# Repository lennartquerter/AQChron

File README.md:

## AQChron

Split Staggered Ortholineair keyboard.

## LICENSE

[CC BY-NC-SA 4.0](./license.md)

## Hardware

Kicad project is in the `hardware` directory.

## Software

TODO

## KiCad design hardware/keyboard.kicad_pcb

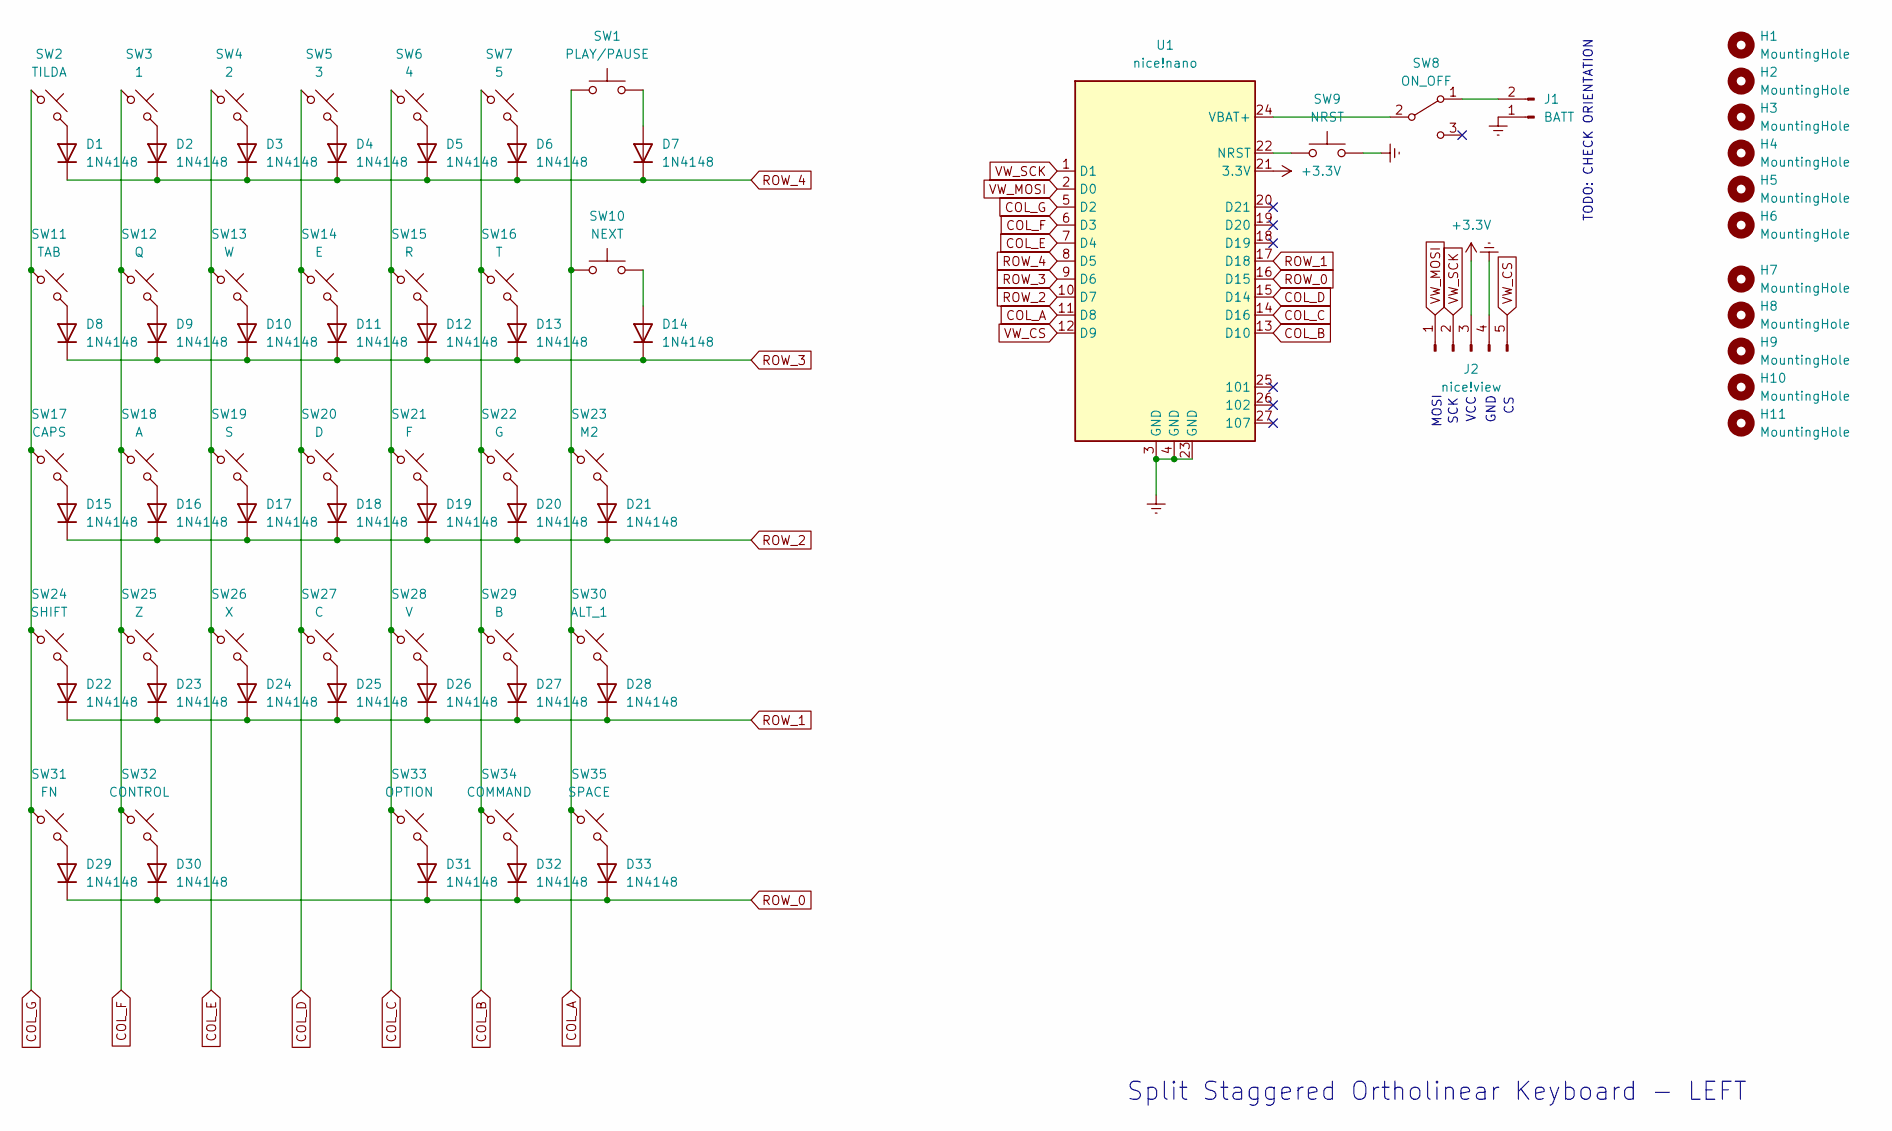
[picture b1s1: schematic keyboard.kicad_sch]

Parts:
D1, D2, D3, D4, D5, D6, D7, D8, D9, D10, D11, D12, D13, D14, D15, D16, D17, D18, D19, D20, D21, D22, D23, D24, D25, D26, D27, D28, D29, D30, D31, D32, D33: 1N4148; D_SMD-THT
H1, H2, H3, H4, H5, H6: MountingHole; MountingPin_M2
H7, H8, H9, H10, H11: MountingHole; MountingPin_M3
J1: BATT; JST_PH_S2B-PH-K_1x02_P2.00mm_Horizontal
J2: nice!view; PinHeader_1x05_P2.54mm_Vertical
SW1: PLAY/PAUSE; SW_PUSH_6mm
SW2: TILDA; Hotswap_Choc_V1V2
SW3: 1; Hotswap_Choc_V1V2
SW4: 2; Hotswap_Choc_V1V2
SW5: 3; Hotswap_Choc_V1V2
SW6: 4; Hotswap_Choc_V1V2
SW7: 5; Hotswap_Choc_V1V2
SW8: ON_OFF; Switch_MSK12C02
SW9: NRST; SW_PUSH_6mm
SW10: NEXT; SW_PUSH_6mm
SW11: TAB; Hotswap_Choc_V1V2
SW12: Q; Hotswap_Choc_V1V2
SW13: W; Hotswap_Choc_V1V2
SW14: E; Hotswap_Choc_V1V2
SW15: R; Hotswap_Choc_V1V2
SW16: T; Hotswap_Choc_V1V2
SW17: CAPS; Hotswap_Choc_V1V2
SW18: A; Hotswap_Choc_V1V2
SW19: S; Hotswap_Choc_V1V2
SW20: D; Hotswap_Choc_V1V2
SW21: F; Hotswap_Choc_V1V2
SW22: G; Hotswap_Choc_V1V2
SW23: M2; Hotswap_Choc_V1V2
SW24: SHIFT; Hotswap_Choc_V1V2
SW25: Z; Hotswap_Choc_V1V2
SW26: X; Hotswap_Choc_V1V2
SW27: C; Hotswap_Choc_V1V2
SW28: V; Hotswap_Choc_V1V2
SW29: B; Hotswap_Choc_V1V2
SW30: ALT_1; Hotswap_Choc_V1V2
SW31: FN; Hotswap_Choc_V1V2
SW32: CONTROL; Hotswap_Choc_V1V2
SW33: OPTION; Hotswap_Choc_V1V2
SW34: COMMAND; Hotswap_Choc_V1V2
SW35: SPACE; Hotswap_Choc_V1V2
U1: nice!nano

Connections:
+3.3V: J2.3, U1.21 (3.3V)
COL_A: SW1.1, SW10.1, SW23.1, SW30.1, SW35.1, U1.11 (D8)
COL_B: SW7.1, SW16.1, SW22.1, SW29.1, SW34.1, U1.13 (D10)
COL_C: SW6.1, SW15.1, SW21.1, SW28.1, SW33.1, U1.14 (D16)
COL_D: SW5.1, SW14.1, SW20.1, SW27.1, U1.15 (D14)
COL_E: SW4.1, SW13.1, SW19.1, SW26.1, U1.7 (D4)
COL_F: SW3.1, SW12.1, SW18.1, SW25.1, SW32.1, U1.6 (D3)
COL_G: SW2.1, SW11.1, SW17.1, SW24.1, SW31.1, U1.5 (D2)
GNDREF: J1.1, J2.4, SW9.2, U1.3 (GND), U1.4 (GND), U1.23 (GND)
unnamed: D1.2 (A), SW2.2
unnamed: D2.2 (A), SW3.2
unnamed: D3.2 (A), SW4.2
unnamed: D4.2 (A), SW5.2
unnamed: D5.2 (A), SW6.2
unnamed: D6.2 (A), SW7.2
unnamed: D7.2 (A), SW1.2
unnamed: D8.2 (A), SW11.2
unnamed: D9.2 (A), SW12.2
unnamed: D10.2 (A), SW13.2
unnamed: D11.2 (A), SW14.2
unnamed: D12.2 (A), SW15.2
unnamed: D13.2 (A), SW16.2
unnamed: D14.2 (A), SW10.2
unnamed: D15.2 (A), SW17.2
unnamed: D16.2 (A), SW18.2
unnamed: D17.2 (A), SW19.2
unnamed: D18.2 (A), SW20.2
unnamed: D19.2 (A), SW21.2
unnamed: D20.2 (A), SW22.2
unnamed: D21.2 (A), SW23.2
unnamed: D22.2 (A), SW24.2
unnamed: D23.2 (A), SW25.2
unnamed: D24.2 (A), SW26.2
unnamed: D25.2 (A), SW27.2
unnamed: D26.2 (A), SW28.2
unnamed: D27.2 (A), SW29.2
unnamed: D28.2 (A), SW30.2
unnamed: D29.2 (A), SW31.2
unnamed: D30.2 (A), SW32.2
unnamed: D31.2 (A), SW33.2
unnamed: D32.2 (A), SW34.2
unnamed: D33.2 (A), SW35.2
unnamed: J1.2, SW8.1 (A)
unnamed: SW8.2 (B), U1.24 (VBAT+)
unnamed: SW9.1, U1.22 (NRST)
ROW_0: D29.1 (K), D30.1 (K), D31.1 (K), D32.1 (K), D33.1 (K), U1.16 (D15)
ROW_1: D22.1 (K), D23.1 (K), D24.1 (K), D25.1 (K), D26.1 (K), D27.1 (K), D28.1 (K), U1.17 (D18)
ROW_2: D15.1 (K), D16.1 (K), D17.1 (K), D18.1 (K), D19.1 (K), D20.1 (K), D21.1 (K), U1.10 (D7)
ROW_3: D8.1 (K), D9.1 (K), D10.1 (K), D11.1 (K), D12.1 (K), D13.1 (K), D14.1 (K), U1.9 (D6)
ROW_4: D1.1 (K), D2.1 (K), D3.1 (K), D4.1 (K), D5.1 (K), D6.1 (K), D7.1 (K), U1.8 (D5)
VW_CS: J2.5, U1.12 (D9)
VW_MOSI: J2.1, U1.2 (D0)
VW_SCK: J2.2, U1.1 (D1)

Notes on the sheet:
GND
VCC
MOSI
Split Staggered Ortholinear Keyboard - LEFT
TODO: CHECK ORIENTATION
SCK

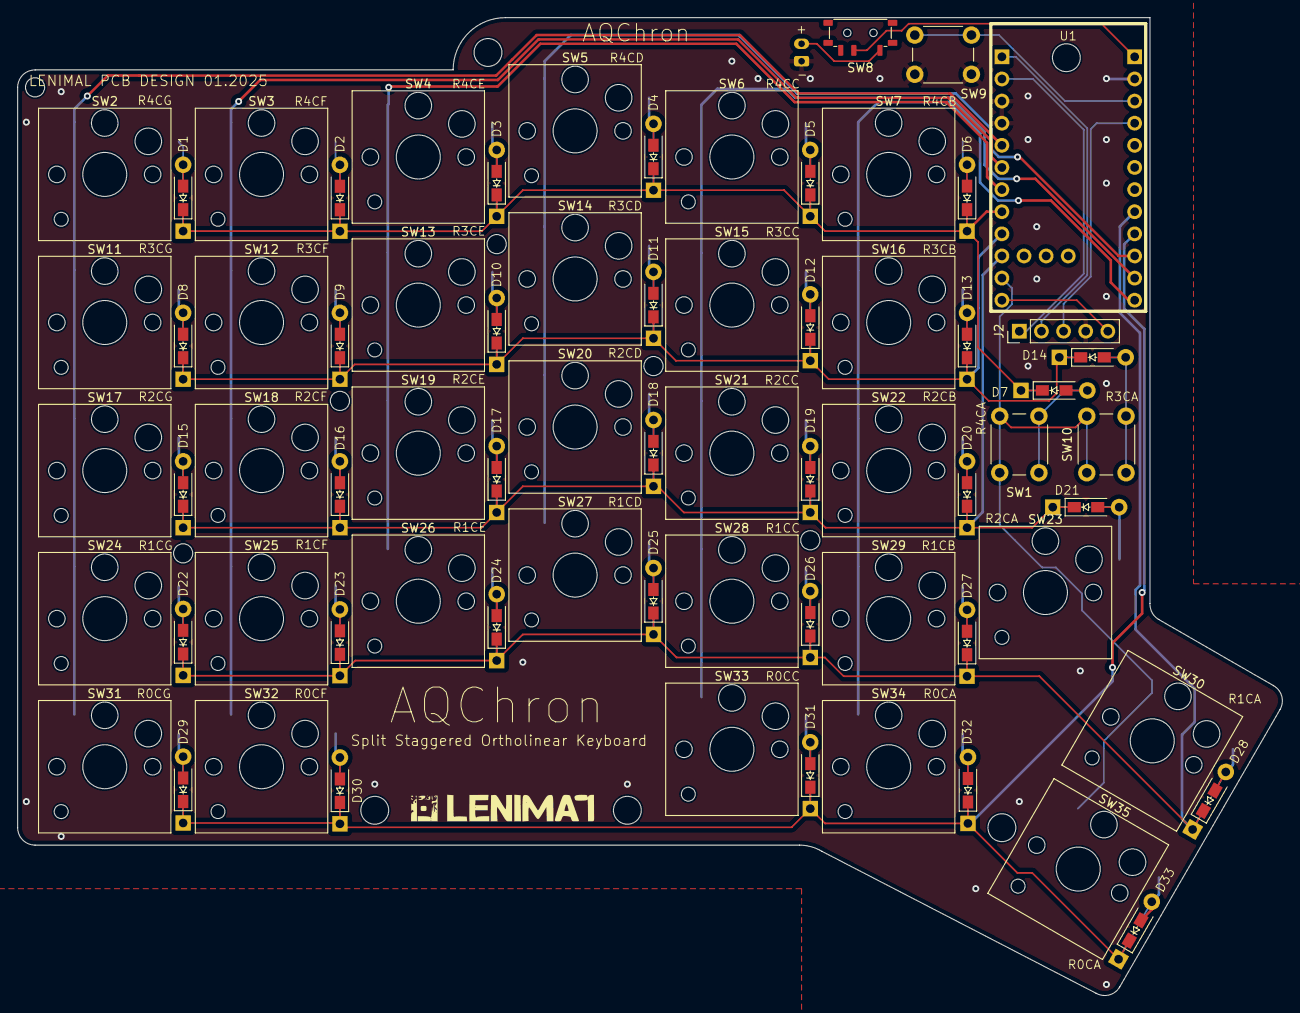
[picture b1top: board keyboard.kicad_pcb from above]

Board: 2 copper layers, 145.2 x 112.3 mm, 82 parts (1 on the bottom side), 53 nets.

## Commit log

2025-01-08 initial commit, setup readme, license and ignore
2025-01-18 finish right keyboard, generate 3D models, add distribution folders
2025-01-20 updated version, ready for production (v1)
